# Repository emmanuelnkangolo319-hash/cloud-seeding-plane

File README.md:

# Cloud-seeding-plane
A rc plane that deposits 150g of salt into clouds to increase chances of rain.

What this plane can do:

-Collect data of the temperature, atmospheric pressure, height and humidity of the air. This data will be used to see how many trips are needed to give the cloud a chance of rain or literally any type of precipitation.

-Take photos and live videos.

-Deposit a maximum of 150g of salt into a cloud.

I made this mainly because i think that Weather Report(from Jo Jos) has one of the coolest powers, and i thought how useful it could be, not for combat, but to help people. I thought that this could be in so many farms, to avoid dry seasons entirely, i believe that humanity is to advanced to keep worrying about food, so im trying to push us in the right direction.

3d model:

https://cad.onshape.com/documents/48e34506531f835c4cff8a26/w/4c8b36f0f4d367943fe0274f/e/af00958ca7866456fd633129?renderMode=0&uiState=6b0963fe7f1bef82e0f034d7
This 3d model should be printed with LW PLA/PLA AERO

I recommend making the air frame out of styrofoam but still reinforced with carbon fiber sheets and epoxy.

Electronics:

I recommend making the ground controls with a perf board.

10x4.5 propellers will be used for this plane.

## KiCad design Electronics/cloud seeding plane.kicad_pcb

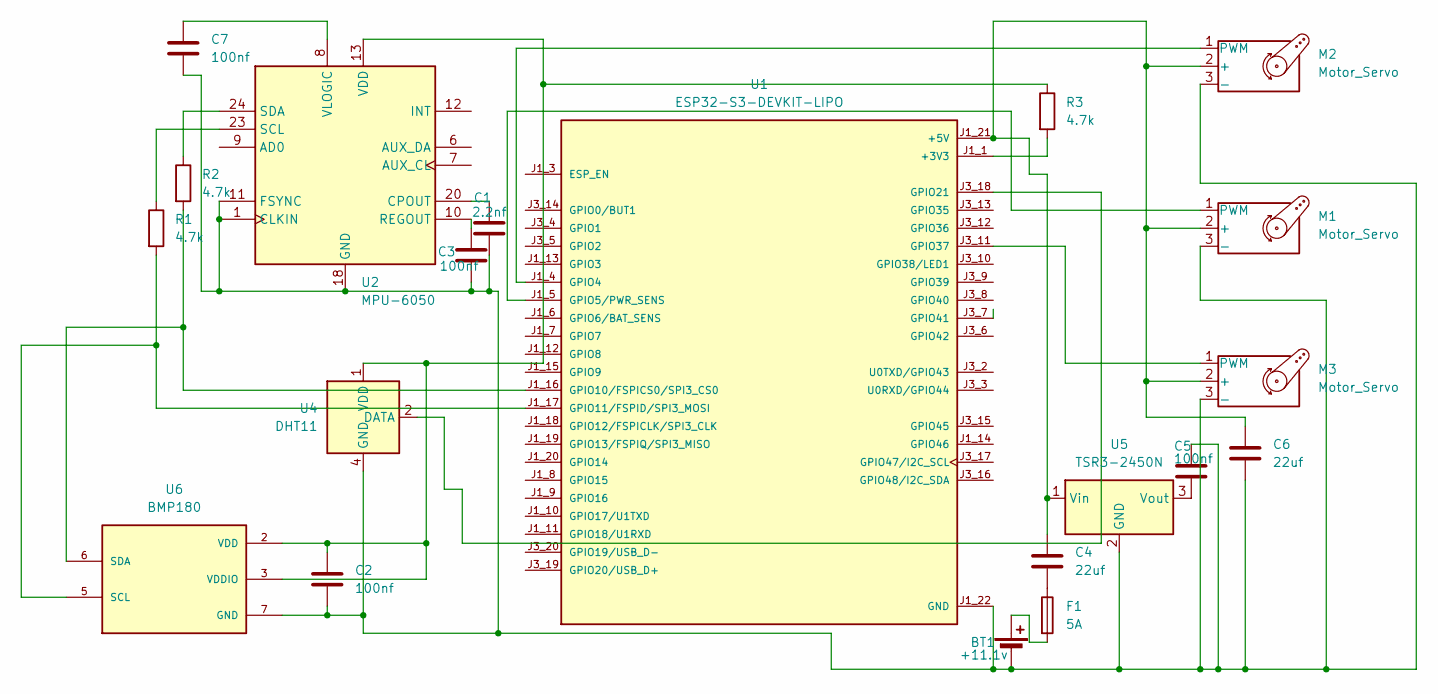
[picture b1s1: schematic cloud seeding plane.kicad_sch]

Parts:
BT1: +11.1v; PinHeader_1x02_P2.54mm_Vertical
C1: 2.2nf; C_0805_2012Metric
C2, C3, C5, C7: 100nf; C_0805_2012Metric
C4: 22uf; C_1206_3216Metric
C6: 22uf; C_0805_2012Metric
F1: 5A; Fuseholder_Blade_Mini_Keystone_3568
M1, M2, M3: Motor_Servo; PinHeader_1x03_P2.54mm_Vertical
R1, R2, R3: 4.7k; R_0805_2012Metric
U1: ESP32-S3-DEVKIT-LIPO; XCVR_ESP32-S3-DEVKIT-LIPO; MPN ESP32-S3-DevKit-Lipo; DigiKey_Part_Number 1188-ESP32-S3-DEVKIT-LIPO-ND
U2: MPU-6050; InvenSense_QFN-24_4x4mm_P0.5mm
U4: DHT11; Aosong_DHT11_5.5x12.0_P2.54mm
U5: TSR3-2450N; Converter_DCDC_TRACO_TSR2-24xxN_TSR2-24xxxN_THT
U6: BMP180; MPN BMP180

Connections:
+3V3: R3.2, U1.J1_1 (+3V3), U1.J1_2 (+3V3)
GND: BT1.2 (-), C1.2, C2.2, C3.2, C5.1, C6.2, C7.2, M1.3 (-), M2.3 (-), M3.3 (-), U1.J1_22 (GND), U1.J3_1 (GND), U1.J3_21 (GND), U1.J3_22 (GND), U2.1 (CLKIN), U2.11 (FSYNC), U2.18 (GND), U4.4 (GND), U5.2 (GND), U6.7 (GND)
unnamed: BT1.1 (+), F1.2
unnamed: C4.2, F1.1
unnamed: C4.1, C6.1, M1.2 (+), M2.2 (+), M3.2 (+), U1.J1_21 (+5V), U5.1 (Vin)
unnamed: M1.1 (PWM), U1.J1_5 (GPIO5/PWR_SENS)
unnamed: M2.1 (PWM), U1.J1_4 (GPIO4)
unnamed: M3.1 (PWM), U1.J3_11 (GPIO37)
unnamed: R2.2, U1.J1_16 (GPIO10/FSPICS0/SPI3_CS0), U6.6 (SDA)
unnamed: R1.2, U1.J1_17 (GPIO11/FSPID/SPI3_MOSI), U6.5 (SCL)
unnamed: U1.J3_18 (GPIO21), U4.2 (DATA)
unnamed: C1.1, U2.20 (CPOUT)
unnamed: C3.1, U2.10 (REGOUT)
unnamed: R1.1, U2.23 (SCL)
unnamed: R2.1, U2.24 (SDA)
unnamed: C2.1, R3.1, U2.13 (VDD), U4.1 (VDD), U6.2 (VDD), U6.3 (VDDIO)
unnamed: C7.1, U2.8 (VLOGIC)
unnamed: C5.2, U5.3 (Vout)

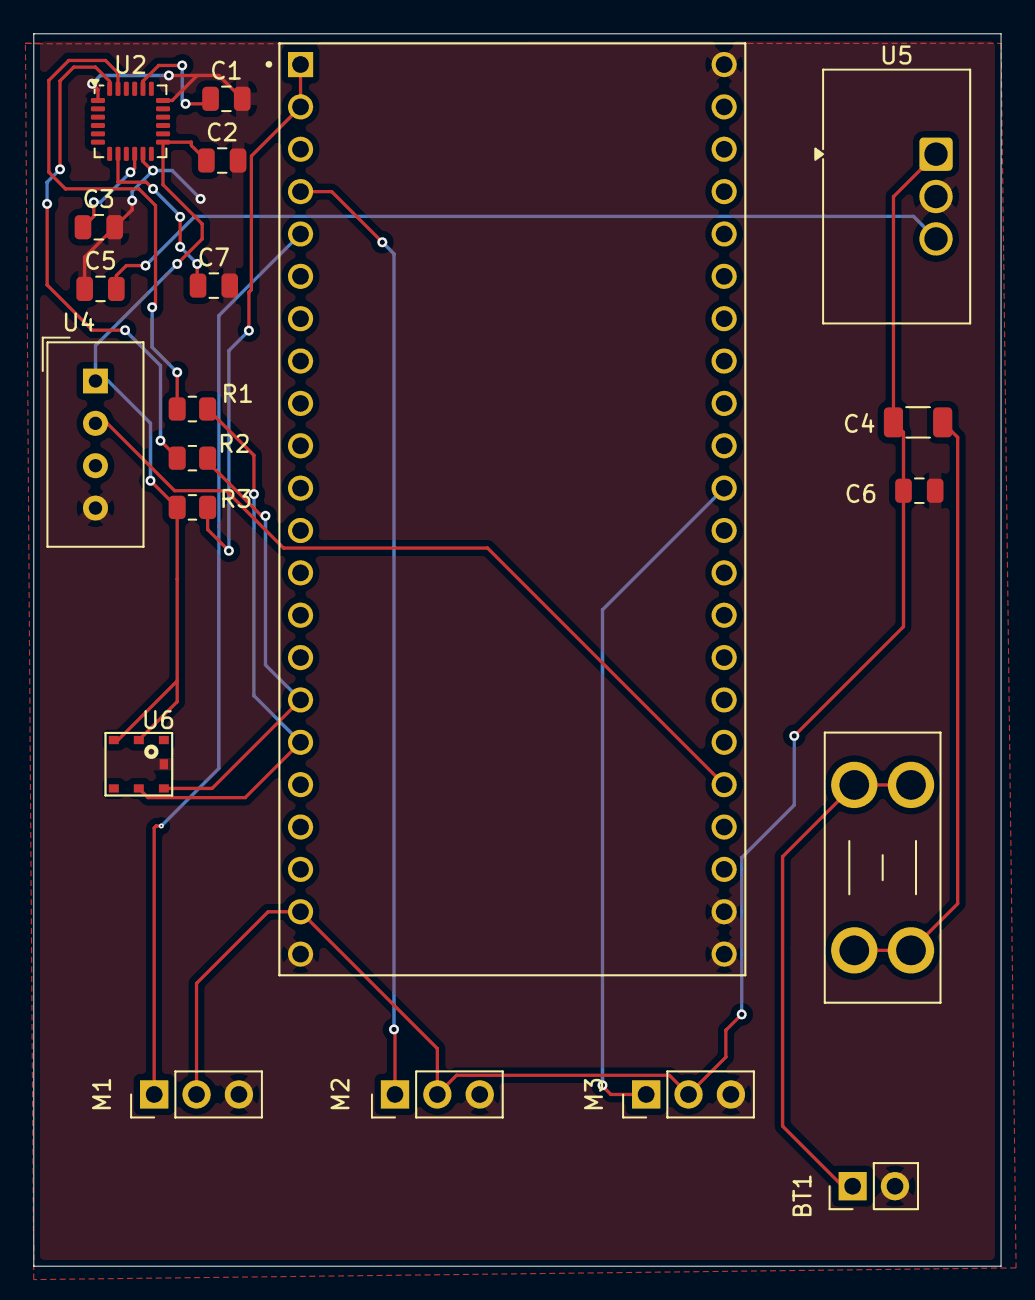
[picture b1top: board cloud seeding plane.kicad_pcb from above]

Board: 2 copper layers, 58.0 x 73.9 mm, 20 parts (0 on the bottom side), 18 nets.
